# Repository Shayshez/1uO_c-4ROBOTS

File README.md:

# 1uO_c-4ROBOTS
1u Ornament and Crime for Intellijel 1u format

Firmware with VOR Support Available here:

https://www.plum-audio.com/firmwares

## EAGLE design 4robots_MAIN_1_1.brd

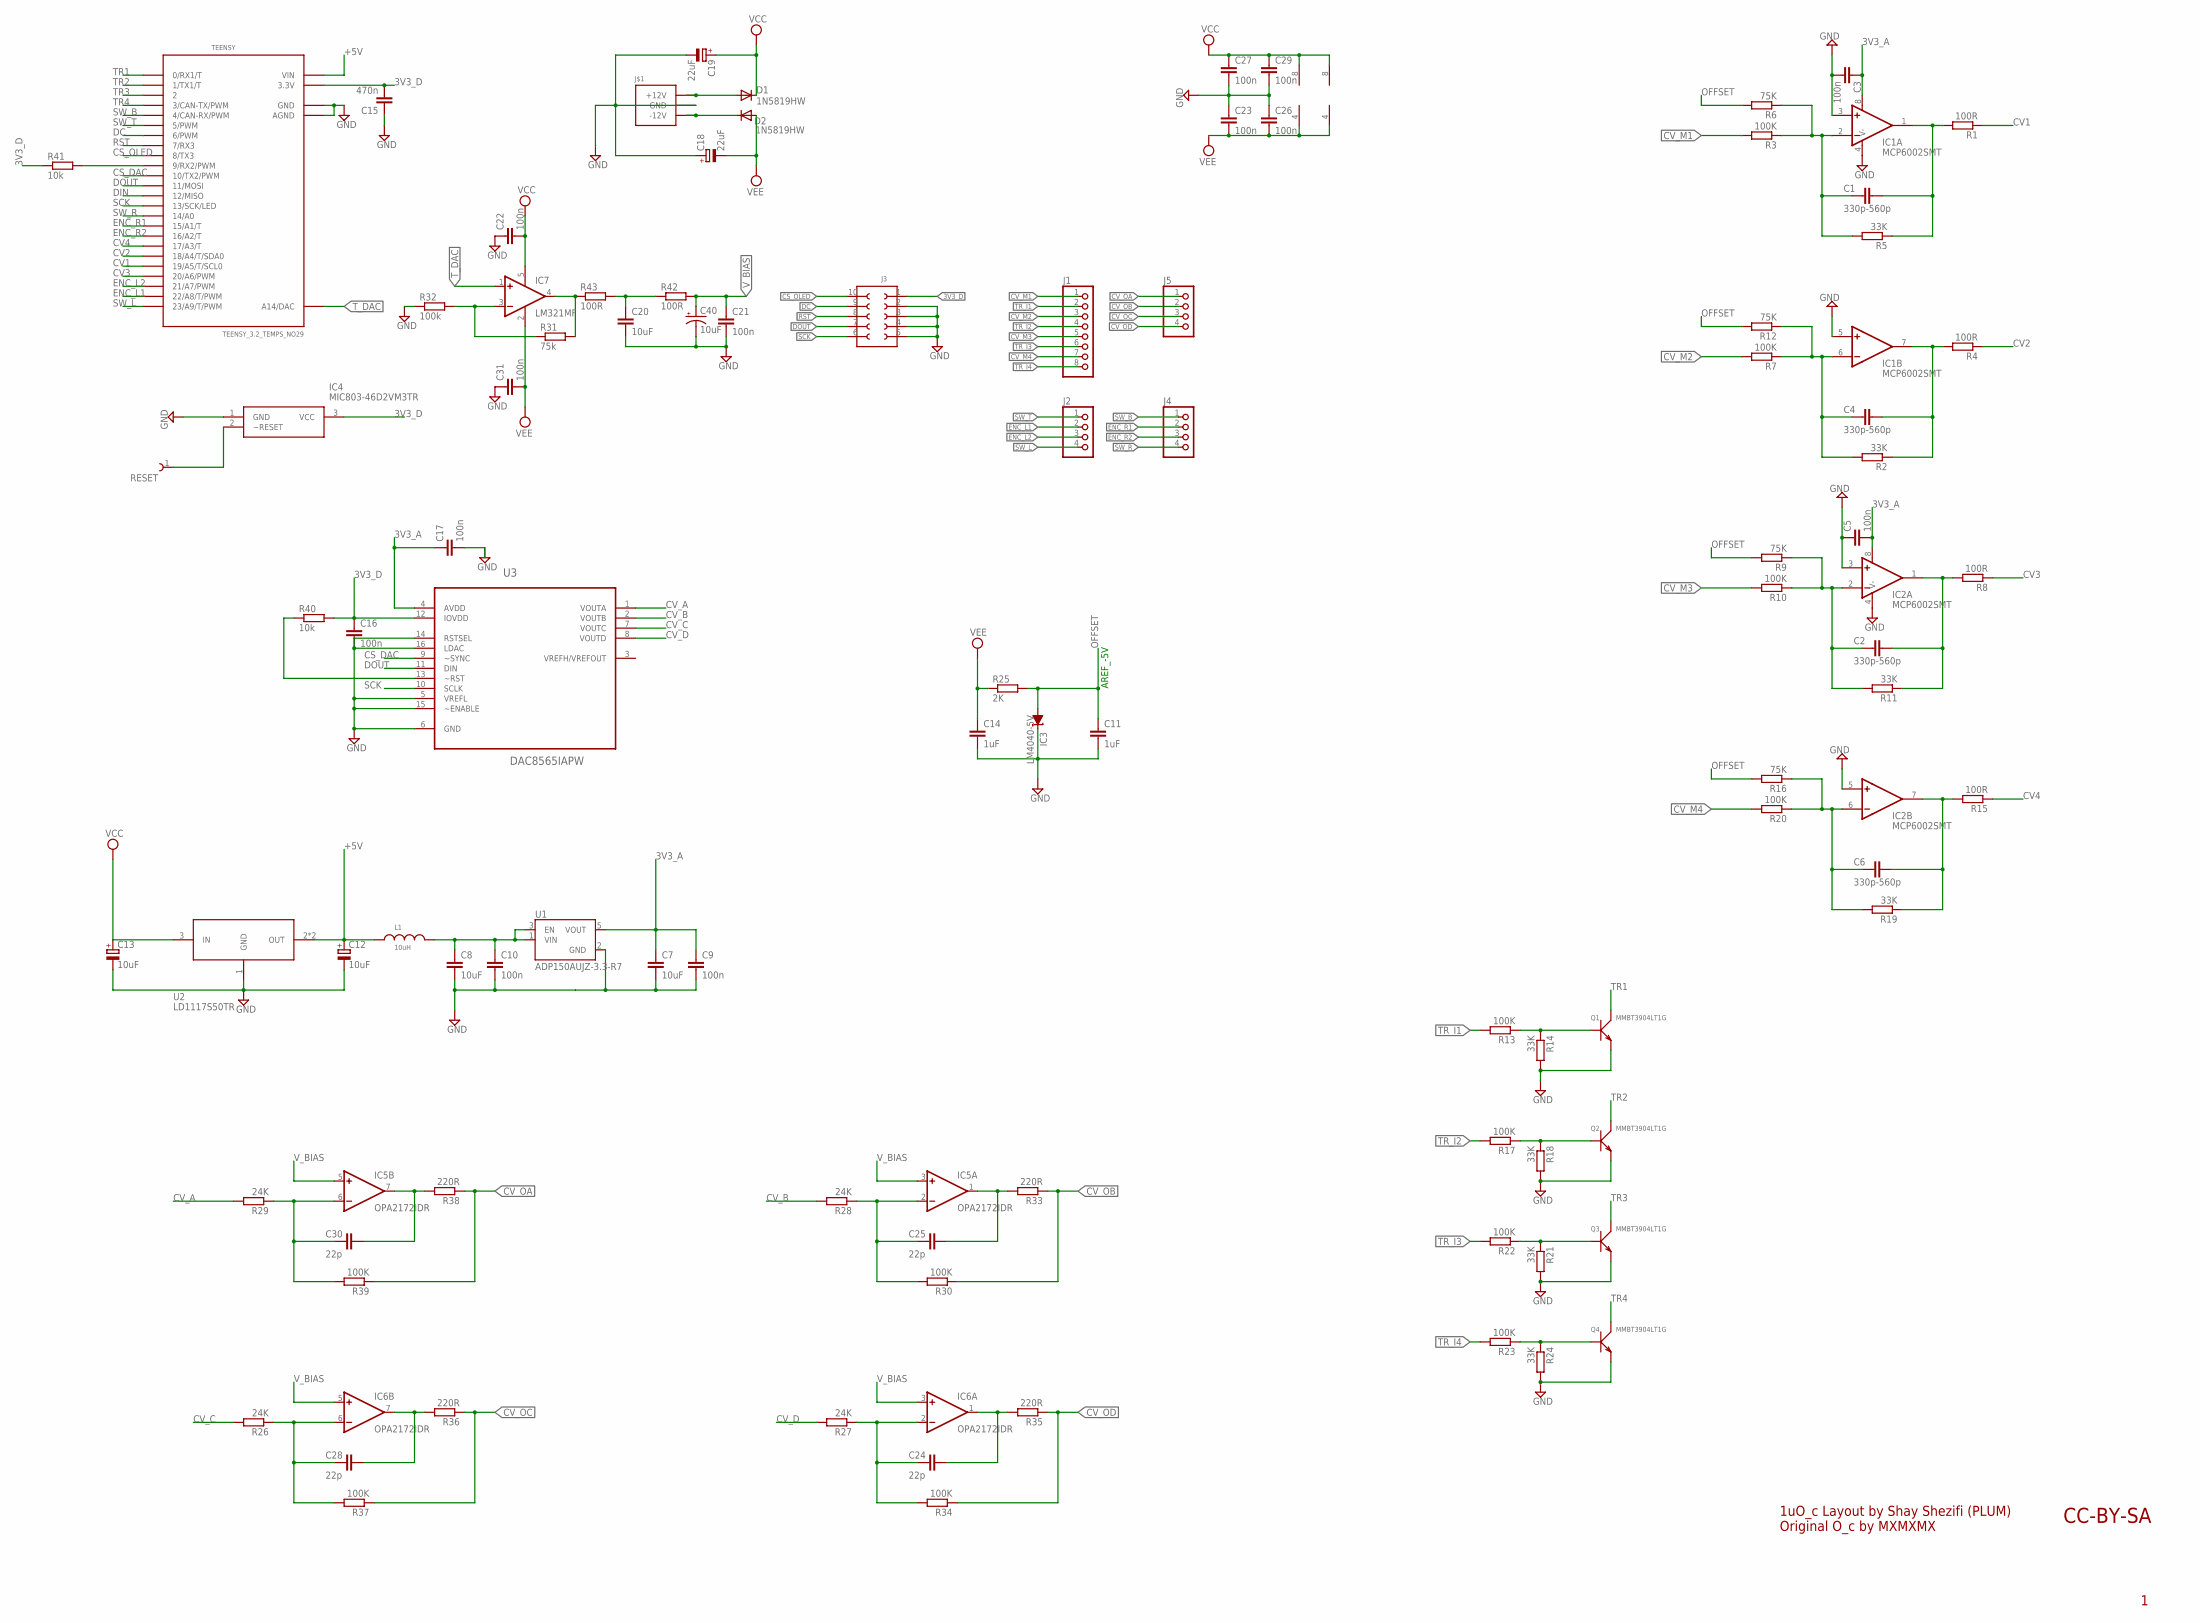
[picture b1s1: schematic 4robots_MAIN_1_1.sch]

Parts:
C1, C2, C4, C6: 330p-560p; C0603
C3, C5, C9, C10, C16, C17, C21, C22, C23, C26, C27, C29, C31: 100n; C0603
C7, C8: 10uF; C1206K
C11, C14: 1uF; C0603
C12, C13: 10uF; PANASONIC_B
C15: 470n; C0603
C18, C19: 22uF; PANASONIC_C
C20: 10uF; C0603
C24, C25, C28, C30: 22p; C0603
C40: 10uF; PANASONIC_A
D1, D2: 1N5819HW; DIODE_SOD123
IC1, IC2: MCP6002SMT; SOIC8
IC3: LM4040-5V; DBZ_R-PDSO-G3
IC4: MIC803-46D2VM3TR; SOT95P230X110-3N
IC5, IC6: OPA2172IDR; SO08
IC7: LM321MF; SOT23-5
J1: PINHD-1X8; 1X08
J2, J4, J5: PINHD-1X4; 1X04
J3: 61301021121
J$1: POWER_SIMPLE10; POWER_10
L1: 10uH; WE-LQ_M
Q1, Q2, Q3, Q4: MMBT3904LT1G; SOT-23
R1, R4, R8, R15, R42, R43: 100R; R0603
R2, R5, R11, R14, R18, R19, R21, R24: 33K; R0603
R3, R7, R10, R13, R17, R20, R22, R23, R30, R34, R37, R39: 100K; R0603
R6, R9, R12, R16: 75K; R0603
R25: 2K; R0603
R26, R27, R28, R29: 24K; R0603
R31: 75k; R0603
R32: 100k; R0603
R33, R35, R36, R38: 220R; R0603
R40, R41: 10k; R0603
RESET: 61300111121
TEENSY: TEENSY_3.2_TEMPS_NO29
U1: ADP150AUJZ-3.3-R7; SOT95P280X100-5N
U2: LD1117S50TR; SOT223
U3: DAC8565IAPW; SOP65P640X120-16N

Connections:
3V3_A: C3.1, C5.2, C7.1, C9.1, C17.1, IC1.8 (V+), IC2.8 (V+), U1.5 (VOUT), U3.4 (AVDD)
3V3_D: C15.2, C16.1, IC4.3 (VCC), J3.1, R40.2, R41.1, TEENSY.3.3V, U3.12 (IOVDD)
+5V: C12.+, L1.1, TEENSY.VIN, U2.2 (OUT), U2.4 (OUT)
CS_DAC: TEENSY.10 (10/TX2/PWM), U3.9 (~SYNC)
CS_OLED: J3.10, TEENSY.8 (8/TX3)
CV1: R1.1, TEENSY.19/A5 (19/A5/T/SCL0)
CV2: R4.1, TEENSY.18/A4 (18/A4/T/SDA0)
CV3: R8.1, TEENSY.20/A6 (20/A6/PWM)
CV4: R15.1, TEENSY.17/A3 (17/A3/T)
CV_A: R29.2, U3.1 (VOUTA)
CV_B: R28.2, U3.2 (VOUTB)
CV_C: R26.2, U3.7 (VOUTC)
CV_D: R27.2, U3.8 (VOUTD)
CV_M1: J1.1, R3.2
CV_M2: J1.3, R7.2
CV_M3: J1.5, R10.2
CV_M4: J1.7, R20.2
CV_OA: J5.1, R38.1, R39.1
CV_OB: J5.2, R30.1, R33.1
CV_OC: J5.3, R36.1, R37.1
CV_OD: J5.4, R34.1, R35.1
DC: J3.9, TEENSY.6 (6/PWM)
DIN: TEENSY.12 (12/MISO)
DOUT: J3.7, TEENSY.11 (11/MOSI), U3.11 (DIN)
ENC_L1: J2.2, TEENSY.22/A8 (22/A8/T/PWM)
ENC_L2: J2.3, TEENSY.21/A7 (21/A7/PWM)
ENC_R1: J4.2, TEENSY.15/A1 (15/A1/T)
ENC_R2: J4.3, TEENSY.16/A2 (16/A2/T)
GND: C3.2, C5.1, C7.2, C8.2, C9.2, C10.2, C11.2, C12.-, C13.-, C14.2, C15.1, C16.2, C17.2, C18.+, C19.-, C20.2, C21.2, C22.1, C23.1, C26.1, C27.2, C29.2, C31.1, C40.-, IC1.3 (+IN), IC1.4 (V-), IC1.5 (+IN), IC2.3 (+IN), IC2.4 (V-), IC2.5 (+IN), IC3.1 (C), IC4.1 (GND), J3.2, J3.3, J3.4, J3.5, J$1.3 (GND), J$1.4 (GND), J$1.5 (GND), J$1.6 (GND), J$1.7 (GND), J$1.8 (GND), Q1.2 (E), Q2.2 (E), Q3.2 (E), Q4.2 (E), R14.2, R18.2, R21.2, R24.2, R32.1, TEENSY.AGND, TEENSY.GND, U1.2 (GND), U2.1 (GND), U3.5 (VREFL), U3.6 (GND), U3.14 (RSTSEL), U3.15 (~ENABLE), U3.16 (LDAC)
unnamed: D2.C, J$1.1 (-12V), J$1.2 (-12V)
unnamed: D1.A, J$1.9 (+12V), J$1.10 (+12V)
unnamed: C8.1, C10.1, L1.2, U1.1 (VIN), U1.3 (EN)
unnamed: IC7.4 (OUT), R31.2, R43.1
unnamed: C1.2, IC1.2 (-IN), R3.1, R5.2, R6.1
unnamed: C1.1, IC1.1 (OUT), R1.2, R5.1
unnamed: IC7.3 (-IN), R31.1, R32.2
unnamed: R40.1, U3.13 (~RST)
unnamed: R41.2, TEENSY.9 (9/RX2/PWM)
unnamed: C4.2, IC1.6 (-IN), R2.2, R7.1, R12.1
unnamed: C4.1, IC1.7 (OUT), R2.1, R4.2
unnamed: C20.1, R42.1, R43.2
unnamed: C2.2, IC2.2 (-IN), R9.1, R10.1, R11.2
unnamed: C2.1, IC2.1 (OUT), R8.2, R11.1
unnamed: C6.2, IC2.6 (-IN), R16.1, R19.2, R20.1
unnamed: C6.1, IC2.7 (OUT), R15.2, R19.1
unnamed: Q1.1 (B), R13.1, R14.1
unnamed: Q2.1 (B), R17.1, R18.1
unnamed: Q3.1 (B), R21.1, R22.1
unnamed: Q4.1 (B), R23.1, R24.1
unnamed: C25.2, IC5.2 (-IN), R28.1, R30.2
unnamed: C30.2, IC5.6 (-IN), R29.1, R39.2
unnamed: C30.1, IC5.7 (OUT), R38.2
unnamed: C25.1, IC5.1 (OUT), R33.2
unnamed: C28.2, IC6.6 (-IN), R26.1, R37.2
unnamed: C28.1, IC6.7 (OUT), R36.2
unnamed: C24.2, IC6.2 (-IN), R27.1, R34.2
unnamed: C24.1, IC6.1 (OUT), R35.2
unnamed: IC4.2 (~RESET), RESET.1
OFFSET: C11.1, IC3.2 (A), R6.2, R9.2, R12.2, R16.2, R25.2
RST: J3.8, TEENSY.7 (7/RX3)
SCK: J3.6, TEENSY.13 (13/SCK/LED), U3.10 (SCLK)
SW_B: J4.1, TEENSY.4 (4/CAN-RX/PWM)
SW_L: J2.4, TEENSY.23/A9 (23/A9/T/PWM)
SW_R: J4.4, TEENSY.14/A0
SW_T: J2.1, TEENSY.5 (5/PWM)
TR1: Q1.3 (C), TEENSY.0 (0/RX1/T)
TR2: Q2.3 (C), TEENSY.1 (1/TX1/T)
TR3: Q3.3 (C), TEENSY.2
TR4: Q4.3 (C), TEENSY.3 (3/CAN-TX/PWM)
TR_I1: J1.2, R13.2
TR_I2: J1.4, R17.2
TR_I3: J1.6, R22.2
TR_I4: J1.8, R23.2
T_DAC: IC7.1 (+IN), TEENSY.RESET/DAC (A14/DAC)
VCC: C13.+, C19.+, C22.2, C27.1, C29.1, D1.C, IC5.8 (V+), IC6.8 (V+), IC7.5 (V+), U2.3 (IN)
VEE: C14.1, C18.-, C23.2, C26.2, C31.2, D2.A, IC5.4 (V-), IC6.4 (V-), IC7.2 (V-), R25.1
V_BIAS: C21.1, C40.+, IC5.3 (+IN), IC5.5 (+IN), IC6.3 (+IN), IC6.5 (+IN), R42.2

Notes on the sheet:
AREF_-5V
1uO_c Layout by Shay Shezifi (PLUM) Original O_c by MXMXMX
CC-BY-SA

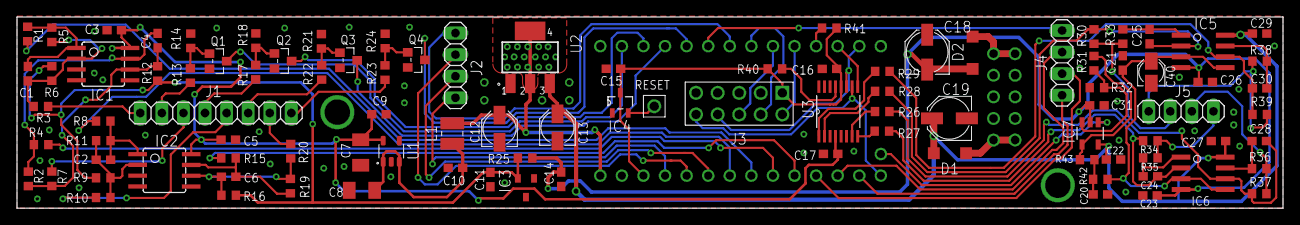
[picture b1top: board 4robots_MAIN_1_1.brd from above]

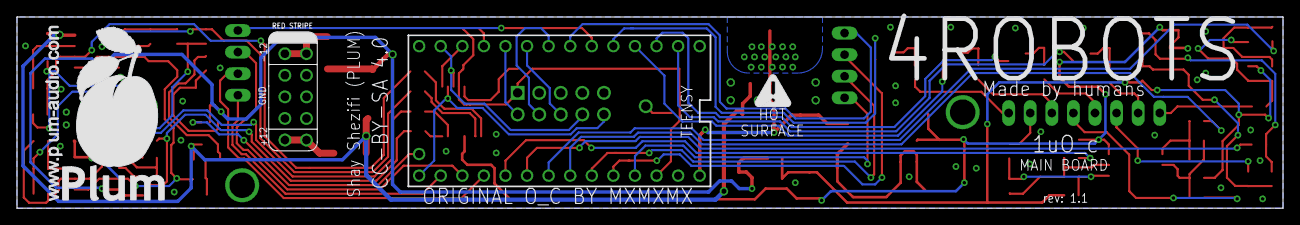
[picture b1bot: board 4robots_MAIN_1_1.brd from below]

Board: 2 copper layers, 149.0 x 22.5 mm, 100 parts (2 on the bottom side), 76 nets.

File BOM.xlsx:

Qty | Value | Device | Package | Parts | Description | ARROW_PART_NUMBER | ARROW_PRICE-STOCK | AVAILABILITY | DESCRIPTION | HEIGHT | MANUFACTURER_NAME | MANUFACTURER_PART_NUMBER | MF | MP | MPN | PACKAGE | PRICE | RS_PART_NUMBER | RS_PRICE-STOCK | SPICEPREFIX | VALUE | WE-NUMBER
 | Resistors
6 | 100R | R-EU_R0603 | R0603 | R1, R4, R8, R15, R42, R43 | RESISTOR, European symbol |  |  |  |  |  |  |  |  |  |  |  |  |  |  | R
4 | 220R | R-EU_R0603 | R0603 | R33, R35, R36, R38 | RESISTOR, European symbol |  |  |  |  |  |  |  |  |  |  |  |  |  |  | R
1 | 2K | R-EU_R0603 | R0603 | R25 | RESISTOR, European symbol |  |  |  |  |  |  |  |  |  |  |  |  |  |  | R
2 | 10k | R-EU_R0603 | R0603 | R40, R41 | RESISTOR, European symbol |  |  |  |  |  |  |  |  |  |  |  |  |  |  | R
4 | 24K | R-EU_R0603 | R0603 | R26, R27, R28, R29 | RESISTOR, European symbol |  |  |  |  |  |  |  |  |  |  |  |  |  |  | R
8 | 33K | R-EU_R0603 | R0603 | R2, R5, R11, R14, R18, R19, R21, R24 | RESISTOR, European symbol |  |  |  |  |  |  |  |  |  |  |  |  |  |  | R
5 | 75K | R-EU_R0603 | R0603 | R6, R9, R12, R16, R31 | RESISTOR, European symbol |  |  |  |  |  |  |  |  |  |  |  |  |  |  | R
13 | 100K | R-EU_R0603 | R0603 | R3, R7, R10, R13, R17, R20, R22, R23, R30 R32,, R34, R37, R39 | RESISTOR, European symbol |  |  |  |  |  |  |  |  |  |  |  |  |  |  | R
 | Caps 0603 >25V
4 | 22p C0G | C-EUC0603 | C0603 | C24, C25, C28, C30 | CAPACITOR, European symbol
4 | 560p C0G | C-EUC0603 | C0603 | C1, C2, C4, C6 | CAPACITOR, European symbol
13 | 100n | C-EUC0603 | C0603 | C3, C5, C9, C10, C16, C17, C21, C22, C23, C26, C27, C29, C31 | CAPACITOR, European symbol
1 | 470n | C-EUC0603 | C0603 | C15 | CAPACITOR, European symbol
2 | 1uF | C-EUC0603 | C0603 | C11, C14 | CAPACITOR, European symbol
1 | 10uF > 10V | C-EUC0603 | C0603 | C20 | CAPACITOR, European symbol
 | Caps 1206
2 | 10uF | C-EUC1206K | C1206K | C7, C8 | CAPACITOR, European symbol
 | Caps electrolytic
2 | 10uF | CPOL-EUB | PANASONIC_B | C12, C13 | POLARIZED CAPACITOR, European symbol |  |  |  |  |  |  |  |  |  |  |  |  |  |  | C
1 | 10uF | CPOL-USA | PANASONIC_A | C40 | POLARIZED CAPACITOR, American symbol
2 | 22uF | CPOL-EUC | PANASONIC_C | C18, C19 | POLARIZED CAPACITOR, European symbol |  |  |  |  |  |  |  |  |  |  |  |  |  |  | C
 | Inductor
1 | 10uH | WE-LQ_1210_744032001 | WE-LQ_M | L1 | SMD Inductor |  |  |  |  |  |  |  |  |  |  |  |  |  |  |  |  | 744032001/1uH
 | IC's
2 | 1N5819HW | DIODE_DIODE-SOD123 | DIODE_SOD123 | D1, D2 | DIODE
1 | ADP150AUJZ-3.3-R7 | ADP150AUJZ-3.3-R7 | SOT95P280X100-5N | U1 | IC REG LINEAR 2V 150MA 5TSOT |  |  | Good | LDO Regulator Pos 2V 0.15A 5-Pin TSOT T/R |  |  |  | Analog Devices | ADP150AUJZ-2.0-R7 |  | TSOT-23 Analog Devices | 0.65 USD
1 | DAC8565IAPW | DAC8565IAPW | SOP65P640X120-16N | U3 | Quad Channel DAC |  |  | Good | 16-Bit, Quad Channel, Ultra-Low Glitch, Voltage Output DAC with 2.5V, 2ppm/C In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 |  |  |  | Texas Instruments | DAC8565IAPW |  | TSSOP-16 Texas Instruments | 10.78 USD
1 | LD1117S50TR | LD1117S50TR | SOT223 | U2 | http://octopart.com/ld1117s50tr-stmicroelectronics-529395 |  |  | Good | LD1117 Series 1300 mA 5 V Fixed Output Positive Voltage LDO Regulator - SOT-223 |  |  |  | STMicroelectronics | LD1117S50TR |  | SOT-223 STMicroelectronics | 0.19 USD
1 | LM321MF | LM321MF | SOT23-5 | IC7 | Low Power Single Op Amp
1 | LM4040-5V | LM4041B12DBZ | DBZ_R-PDSO-G3 | IC3 | PRECISION MICROPOWER SHUNT VOLTAGE REFERENCE
2 | MCP6002SMT | MCP6002SMT | SOIC8 | IC1, IC2 | Dual General Op Amp
1 | MIC803-46D2VM3TR | MIC803-46D2VM3TR | SOT95P230X110-3N | IC4 | 3-pin Microprocessor Supervosor Circui | MIC803-46D2VM3TR |  |  | 3-pin Microprocessor Supervosor Circui | mm | Micrel | MIC803-46D2VM3TR
4 | MMBT3904LT1G | SMD-TRANSISTORS-NPN-40V-200MA-MMBT3904LT1G(SOT-23) | SOT-23 | Q1, Q2, Q3, Q4 | 305010013 |  |  |  |  |  |  |  |  |  | MMBT3904LT1G |  |  |  |  |  | MMBT3904LT1G
2 | TL072D | TL072D | SO08 | IC5, IC6 | OP AMP
1 | TEENSY_3.2_TEMPS_NO29 | TEENSY_3.2_TEMPS_NO29 | TEENSY_3.2_TEMPS_NO29 | TEENSY
 | PIN HEADERS MALE
1 | POWER Header | PINHD-2X5 | 2X5 | Power
1 |  | PINHD-2X5 | 2X5 | J3 | WR-PHD 2.54mm Dual Pin Header, 10 Pins =>Code : Con_BTB_PHD_2.54_2_61301021121
3 |  | PINHD-1X4 | 1X04 | J2, J4, J5 | PIN HEADER
1 |  | PINHD-1X8 | 1X08 | J1 | PIN HEADER

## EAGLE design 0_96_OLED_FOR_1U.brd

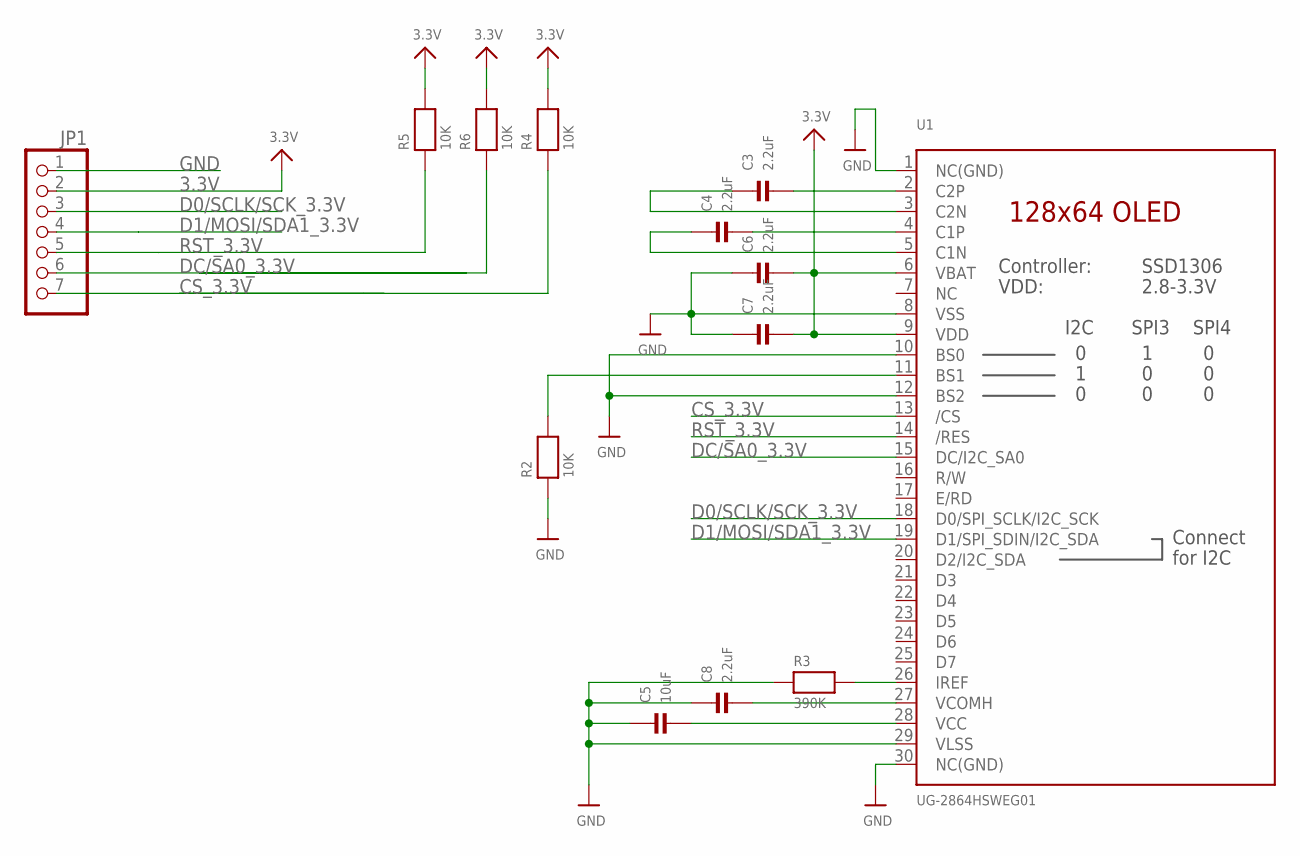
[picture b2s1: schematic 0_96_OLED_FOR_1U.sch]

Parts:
C3, C4, C6, C7, C8: 2.2uF; 0603-MINI
C5: 10uF; 0603-MINI
JP1: HEADER-1X7ROUND; 1X07_ROUND
R2, R4, R5, R6: 10K; 0603-MINI
R3: 390K; 0603-MINI
U1: UG-2864HSWEG01; MICROBUILDER_UG-2864HSWEG01_0.96IN_WRAPAROUND

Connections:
3.3V: C6.2, C7.2, JP1.2, R4.2, R5.2, R6.2, U1.6 (VBAT), U1.9 (VDD)
CS_3.3V: JP1.7, R4.1, U1.13 (/CS)
D0/SCLK/SCK_3.3V: JP1.3, U1.18 (D0/SPI_SCLK/I2C_SCK)
D1/MOSI/SDA1_3.3V: JP1.4, U1.19 (D1/SPI_SDIN/I2C_SDA)
DC/SA0_3.3V: JP1.6, R6.1, U1.15 (DC/I2C_SA0)
GND: C5.1, C6.1, C7.1, C8.1, JP1.1, R2.1, R3.1, U1.1 (NC(GND)), U1.8 (VSS), U1.10 (BS0), U1.12 (BS2), U1.29 (VLSS), U1.30 (NC(GND))
unnamed: R2.2, U1.11 (BS1)
unnamed: R3.2, U1.26 (IREF)
unnamed: C3.2, U1.2 (C2P)
unnamed: C3.1, U1.3 (C2N)
unnamed: C4.2, U1.4 (C1P)
unnamed: C4.1, U1.5 (C1N)
unnamed: C5.2, U1.28 (VCC)
unnamed: C8.2, U1.27 (VCOMH)
RST_3.3V: JP1.5, R5.1, U1.14 (/RES)

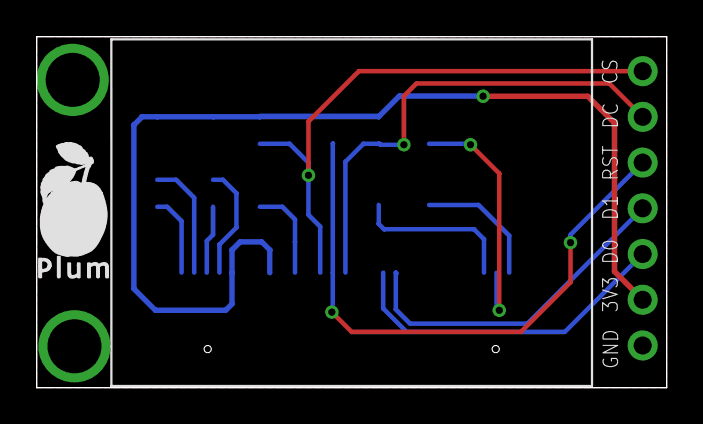
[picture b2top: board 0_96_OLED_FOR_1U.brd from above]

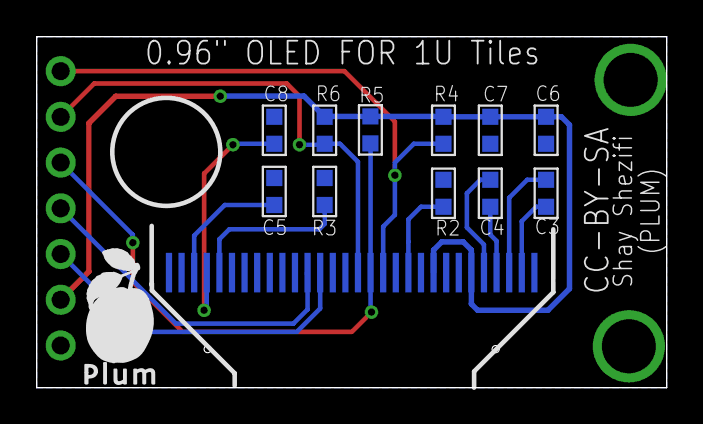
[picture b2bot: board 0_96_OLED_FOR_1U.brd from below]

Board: 2 copper layers, 35.0 x 19.5 mm, 13 parts (11 on the bottom side), 15 nets.

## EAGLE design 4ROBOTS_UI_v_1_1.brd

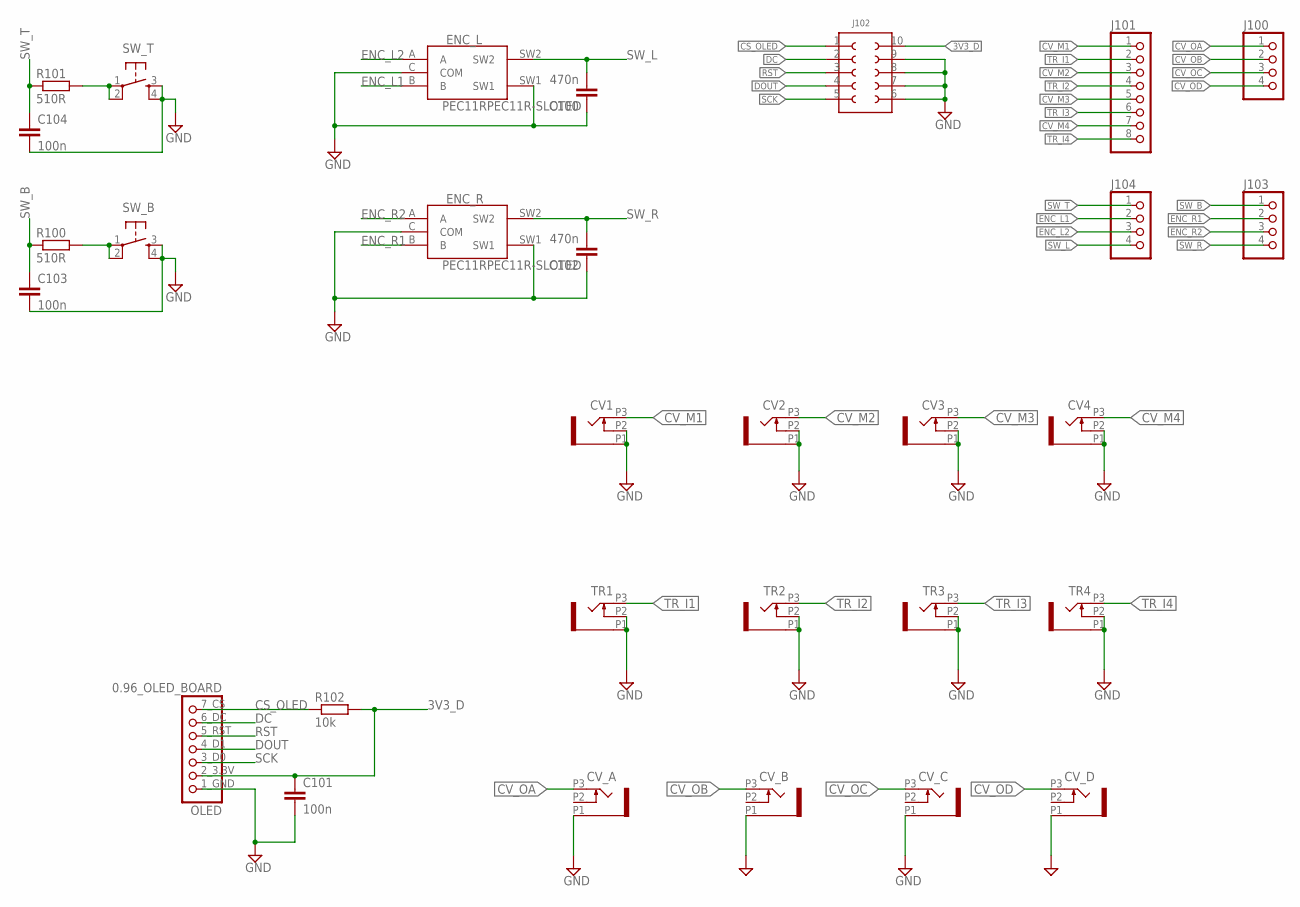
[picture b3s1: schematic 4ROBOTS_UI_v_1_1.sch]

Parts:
C100, C102: 470n; C0603
C101, C103, C104: 100n; C0603
CV1, CV2, CV3, CV4: OG-PJ301_PJ301_THONKICONN6; OG-PJ301_WQP_PJ_301M6
CV_A: OG-PJ301_PJ301_THONKICONN6; OG-PJ301_WQP_PJ_301M6
CV_B: OG-PJ301_PJ301_THONKICONN6; OG-PJ301_WQP_PJ_301M6
CV_C: OG-PJ301_PJ301_THONKICONN6; OG-PJ301_WQP_PJ_301M6
CV_D: OG-PJ301_PJ301_THONKICONN6; OG-PJ301_WQP_PJ_301M6
ENC_L: PEC11RPEC11R-SLOTED; PEC11R-SLOTED
ENC_R: PEC11RPEC11R-SLOTED; PEC11R-SLOTED
J100, J103, J104: PINHD-1X4; 1X04
J101: PINHD-1X8; 1X08
J102: 61301021121
OLED: 0.96_OLED_BOARD
R100, R101: 510R; R0603
R102: 10k; R0603
SW_B: TAC_SWITCHPTH; TACTILE-PTH
SW_T: TAC_SWITCHPTH; TACTILE-PTH
TR1, TR2, TR3, TR4: OG-PJ301_PJ301_THONKICONN6; OG-PJ301_WQP_PJ_301M6

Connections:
3V3_D: C101.1, J102.10, OLED.2_3.3V (3V3), R102.2
CS_OLED: J102.1, OLED.7_CS (CS), R102.1
CV_M1: CV1.P3 (3), J101.1
CV_M2: CV2.P3 (3), J101.3
CV_M3: CV3.P3 (3), J101.5
CV_M4: CV4.P3 (3), J101.7
CV_OA: CV_A.P3 (3), J100.1
CV_OB: CV_B.P3 (3), J100.2
CV_OC: CV_C.P3 (3), J100.3
CV_OD: CV_D.P3 (3), J100.4
DC: J102.2, OLED.6_DC (DC)
DOUT: J102.4, OLED.4_D1 (D1)
ENC_L1: ENC_L.B, J104.2
ENC_L2: ENC_L.A, J104.3
ENC_R1: ENC_R.B, J103.2
ENC_R2: ENC_R.A, J103.3
GND: C100.1, C101.2, C102.1, C103.2, C104.2, CV1.P1 (1), CV1.P2 (2), CV2.P1 (1), CV2.P2 (2), CV3.P1 (1), CV3.P2 (2), CV4.P1 (1), CV4.P2 (2), CV_A.P1 (1), CV_B.P1 (1), CV_C.P1 (1), CV_D.P1 (1), ENC_L.C (COM), ENC_L.SW1, ENC_R.C (COM), ENC_R.SW1, J102.6, J102.7, J102.8, J102.9, OLED.1_GND (GND), SW_B.3, SW_B.4, SW_T.3, SW_T.4, TR1.P1 (1), TR1.P2 (2), TR2.P1 (1), TR2.P2 (2), TR3.P1 (1), TR3.P2 (2), TR4.P1 (1), TR4.P2 (2)
unnamed: R101.2, SW_T.1, SW_T.2
unnamed: R100.2, SW_B.1, SW_B.2
RST: J102.3, OLED.5_RST (RST)
SCK: J102.5, OLED.3_D0 (D0)
SW_B: C103.1, J103.1, R100.1
SW_L: C100.2, ENC_L.SW2, J104.4
SW_R: C102.2, ENC_R.SW2, J103.4
SW_T: C104.1, J104.1, R101.1
TR_I1: J101.2, TR1.P3 (3)
TR_I2: J101.4, TR2.P3 (3)
TR_I3: J101.6, TR3.P3 (3)
TR_I4: J101.8, TR4.P3 (3)

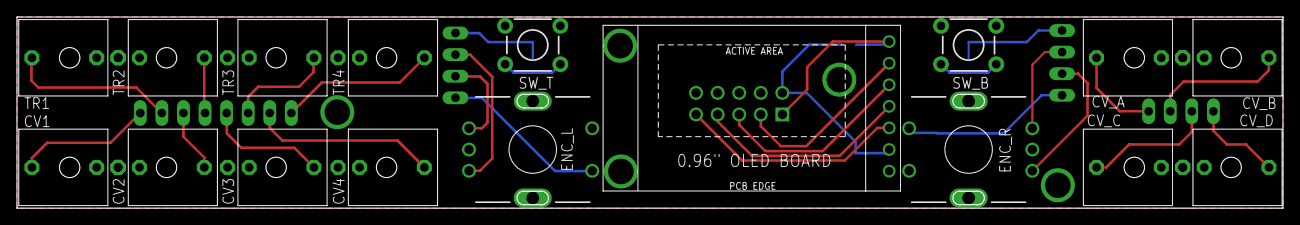
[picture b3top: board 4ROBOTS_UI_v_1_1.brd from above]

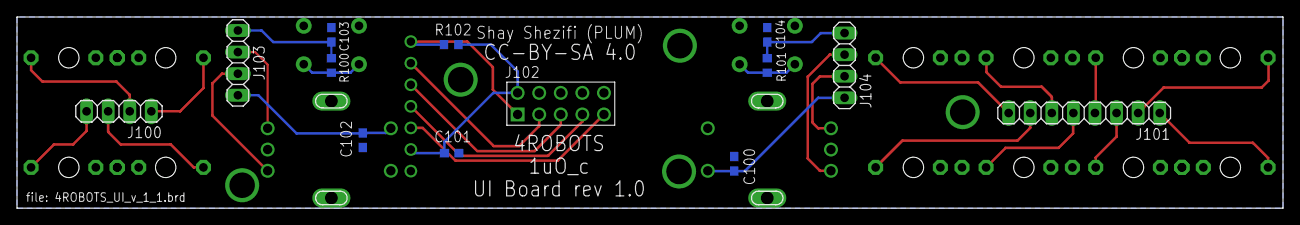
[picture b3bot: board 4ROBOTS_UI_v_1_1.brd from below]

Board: 2 copper layers, 149.0 x 22.5 mm, 30 parts (13 on the bottom side), 29 nets.

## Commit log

2020-01-29 Mouser refs added

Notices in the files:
4ROBOTS_UI_v_1_1.brd:
CC-BY-SA 4.0
parts and their libraries:
Wurth_Elektronik_Electromechanic_Board_t: Copyright: Würth Elektronik
